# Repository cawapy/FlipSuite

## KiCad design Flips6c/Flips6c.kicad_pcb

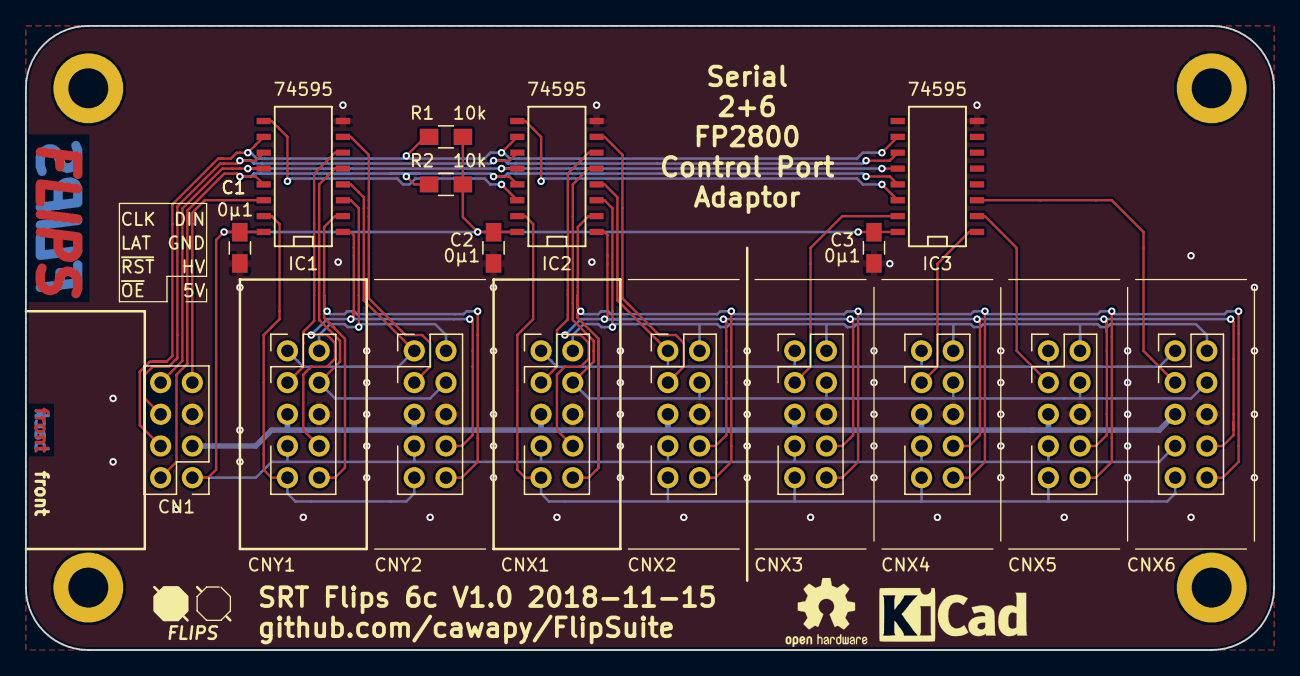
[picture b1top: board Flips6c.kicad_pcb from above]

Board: 2 copper layers, 100.0 x 50.0 mm, 17 parts (0 on the bottom side), 30 nets.

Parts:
C1, C2, C3: 0µ1; C_0805_HandSoldering
CN1: Conn_02x04_Odd_Even; Pin_Header_Straight_2x04_Pitch2.54mm
CNX1, CNX2, CNX3, CNX4, CNX5, CNX6: UFP2810; Pin_Header_Straight_Shrouded_2x05_Pitch2.54mm
CNY1, CNY2: UFP2810; Pin_Header_Straight_Shrouded_2x05_Pitch2.54mm
IC1, IC2, IC3: 74595; SO-16-N
R1, R2: 10k; R_0805_HandSoldering

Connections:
+5V: C1.1, C2.1, C3.1, CN1.1, CNX1.7, CNX2.7, CNX3.7, CNX4.7, CNX5.7, CNX6.7, CNY1.7, CNY2.7, IC1.16, IC2.16, IC3.16, R1.2, R2.2
+12V: CN1.3, CNX1.5, CNX2.5, CNX3.5, CNX4.5, CNX5.5, CNX6.5, CNY1.5, CNY2.5
/DIN: CN1.7, IC1.14
/RCLK: CN1.8, IC1.12, IC2.12, IC3.12
/SRCLK: CN1.6, IC1.11, IC2.11, IC3.11
/XA.0: CNX1.9, CNX2.9, CNX3.9, CNX4.9, CNX5.9, CNX6.9, IC2.15
/XA.1: CNX1.8, CNX2.8, CNX3.8, CNX4.8, CNX5.8, CNX6.8, IC2.1
/XA.2: CNX1.10, CNX2.10, CNX3.10, CNX4.10, CNX5.10, CNX6.10, IC2.2
/XB.0: CNX1.2, CNX2.2, CNX3.2, CNX4.2, CNX5.2, CNX6.2, IC2.3
/XB.1: CNX1.1, CNX2.1, CNX3.1, CNX4.1, CNX5.1, CNX6.1, IC2.4
/XDAT: CNX1.4, CNX2.4, CNX3.4, CNX4.4, CNX5.4, CNX6.4, IC2.5
/XEN1: CNX1.3, IC2.6
/XEN2: CNX2.3, IC2.7
/XEN3: CNX3.3, IC3.15
/XEN4: CNX4.3, IC3.1
/XEN5: CNX5.3, IC3.2
/XEN6: CNX6.3, IC3.3
/YA.0: CNY1.9, CNY2.9, IC1.15
/YA.1: CNY1.8, CNY2.8, IC1.1
/YA.2: CNY1.10, CNY2.10, IC1.2
/YB.0: CNY1.2, CNY2.2, IC1.3
/YB.1: CNY1.1, CNY2.1, IC1.4
/YDAT: CNY1.4, CNY2.4, IC1.5
/YEN1: CNY1.3, IC1.6
/YEN2: CNY2.3, IC1.7
/~OE: CN1.2, IC1.13, IC2.13, IC3.13, R2.1
/~SRCLR: CN1.4, IC1.10, IC2.10, IC3.10, R1.1
GND: C1.2, C2.2, C3.2, CN1.5, CNX1.6, CNX2.6, CNX3.6, CNX4.6, CNX5.6, CNX6.6, CNY1.6, CNY2.6, IC1.8, IC2.8, IC3.8
unnamed: IC1.9, IC2.14
unnamed: IC2.9, IC3.14

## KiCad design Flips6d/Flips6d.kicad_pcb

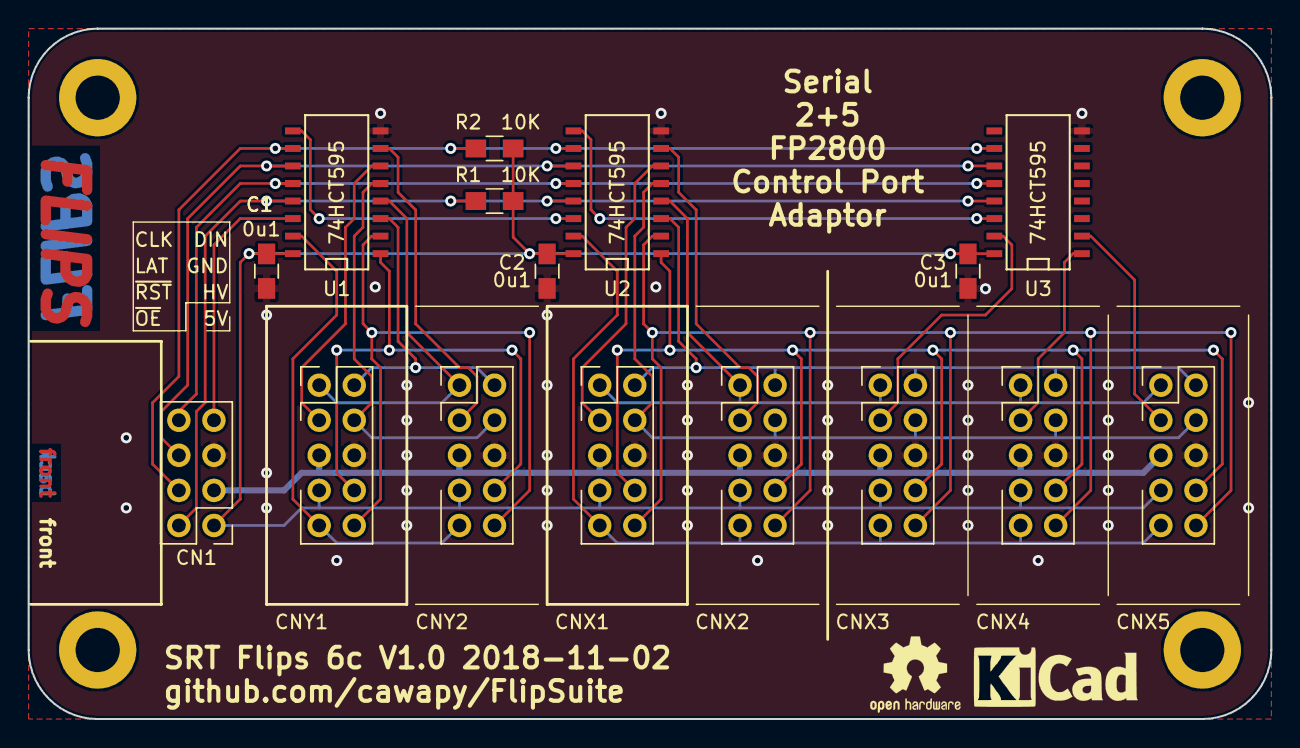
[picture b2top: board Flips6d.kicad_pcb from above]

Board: 2 copper layers, 90.0 x 50.0 mm, 16 parts (0 on the bottom side), 29 nets.

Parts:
C1, C2, C3: 0u1; C_0805_HandSoldering
CN1: Conn_02x04_Odd_Even; Pin_Header_Straight_2x04_Pitch2.54mm
CNX1, CNX2, CNX3, CNX4, CNX5: UFP2810; Pin_Header_Straight_Shrouded_2x05_Pitch2.54mm
CNY1, CNY2: UFP2810; Pin_Header_Straight_Shrouded_2x05_Pitch2.54mm
R1, R2: 10K; R_0805_HandSoldering
U1, U2, U3: 74HCT595; SO-16-N

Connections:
+5V: C1.1, C2.1, C3.1, CN1.1, CNX1.7, CNX2.7, CNX3.7, CNX4.7, CNX5.7, CNY1.7, CNY2.7, R1.2, R2.2, U1.16, U2.16, U3.16
+12V: CN1.3, CNX1.5, CNX2.5, CNX3.5, CNX4.5, CNX5.5, CNY1.5, CNY2.5
/DIN: CN1.7, U1.14
/RCLK: CN1.8, U1.12, U2.12, U3.12
/SRCLK: CN1.6, U1.11, U2.11, U3.11
/XA.0: CNX1.9, CNX2.9, CNX3.9, CNX4.9, CNX5.9, U2.15
/XA.1: CNX1.8, CNX2.8, CNX3.8, CNX4.8, CNX5.8, U2.1
/XA.2: CNX1.10, CNX2.10, CNX3.10, CNX4.10, CNX5.10, U2.2
/XB.0: CNX1.2, CNX2.2, CNX3.2, CNX4.2, CNX5.2, U2.3
/XB.1: CNX1.1, CNX2.1, CNX3.1, CNX4.1, CNX5.1, U2.4
/XDAT: CNX1.4, CNX2.4, CNX3.4, CNX4.4, CNX5.4, U2.5
/XEN1: CNX1.3, U2.6
/XEN2: CNX2.3, U2.7
/XEN3: CNX3.3, U3.15
/XEN4: CNX4.3, U3.1
/XEN5: CNX5.3, U3.2
/YA.0: CNY1.9, CNY2.9, U1.15
/YA.1: CNY1.8, CNY2.8, U1.1
/YA.2: CNY1.10, CNY2.10, U1.2
/YB.0: CNY1.2, CNY2.2, U1.3
/YB.1: CNY1.1, CNY2.1, U1.4
/YDAT: CNY1.4, CNY2.4, U1.5
/YEN1: CNY1.3, U1.6
/YEN2: CNY2.3, U1.7
/~OE: CN1.2, R1.1, U1.13, U2.13, U3.13
/~SRCLR: CN1.4, R2.1, U1.10, U2.10, U3.10
GND: C1.2, C2.2, C3.2, CN1.5, CNX1.6, CNX2.6, CNX3.6, CNX4.6, CNX5.6, CNY1.6, CNY2.6, U1.8, U2.8, U3.8
unnamed: U1.9, U2.14
unnamed: U2.9, U3.14

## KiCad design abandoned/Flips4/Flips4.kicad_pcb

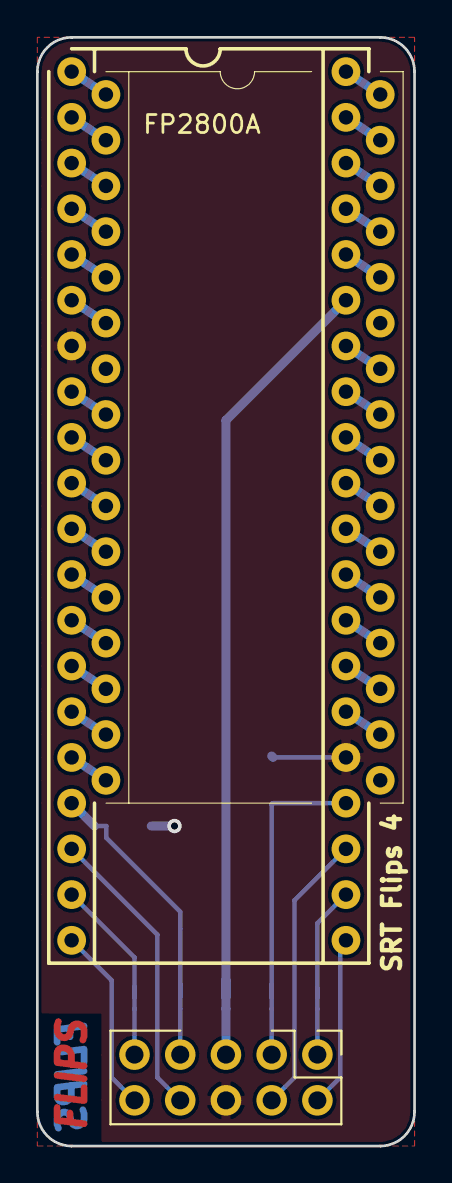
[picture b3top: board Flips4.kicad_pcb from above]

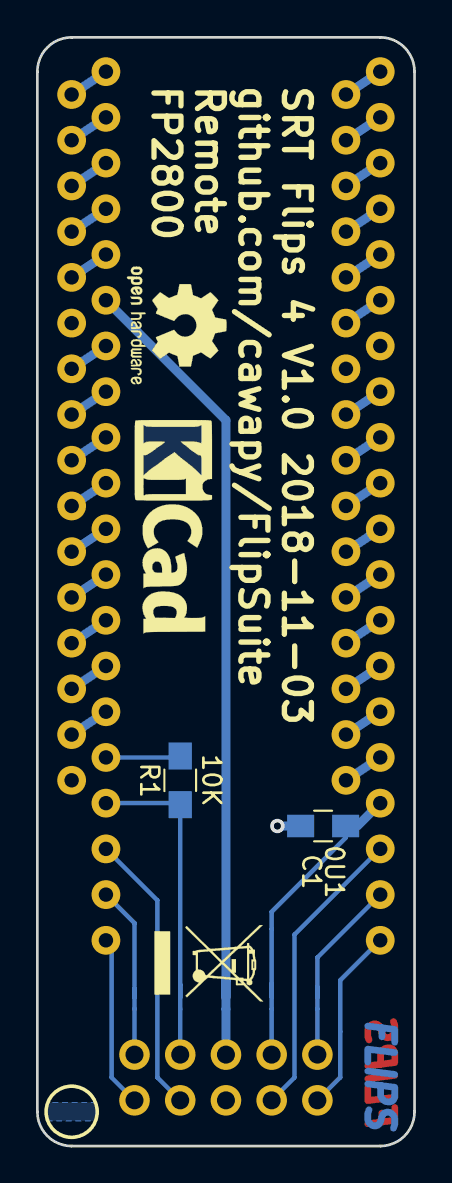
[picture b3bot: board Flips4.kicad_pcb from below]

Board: 2 copper layers, 21.0 x 61.6 mm, 5 parts (2 on the bottom side), 39 nets.

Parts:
C1: 0U1; C_0805_HandSoldering
CN1: UFP2810; Pin_Header_Straight_Shrouded_2x05_Pitch2.54mm
CN2: Conn_02x16_Counter_Clockwise; DIP-32_W15.24mm
R1: 10K; R_0805_HandSoldering
U1: FP2800A; DIP-40_W15.24mm_Socket

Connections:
+12V: CN1.5, U1.35
/A0: CN1.9, U1.19
/A1: CN1.8, U1.18
/A2: CN1.10, U1.20
/B0: CN1.2, U1.21
/B1: CN1.1, U1.22
/Data: CN1.4, U1.23
/Enable: CN1.3, R1.1, U1.24
GND: C1.2, CN1.6, R1.2, U1.7, U1.25
unnamed: CN2.1, U1.1
unnamed: CN2.2, U1.2
unnamed: CN2.3, U1.3
unnamed: CN2.4, U1.4
unnamed: CN2.5, U1.5
unnamed: CN2.6, U1.6
unnamed: CN2.8, U1.8
unnamed: CN2.9, U1.9
unnamed: CN2.10, U1.10
unnamed: CN2.11, U1.11
unnamed: CN2.12, U1.12
unnamed: CN2.13, U1.13
unnamed: CN2.14, U1.14
unnamed: CN2.15, U1.15
unnamed: CN2.16, U1.16
unnamed: CN2.18, U1.26
unnamed: CN2.19, U1.27
unnamed: CN2.20, U1.28
unnamed: CN2.21, U1.29
unnamed: CN2.22, U1.30
unnamed: CN2.23, U1.31
unnamed: CN2.24, U1.32
unnamed: CN2.25, U1.33
unnamed: CN2.26, U1.34
unnamed: CN2.28, U1.36
unnamed: CN2.29, U1.37
unnamed: CN2.30, U1.38
unnamed: CN2.31, U1.39
unnamed: CN2.32, U1.40
VCC: C1.1, CN1.7, U1.17
